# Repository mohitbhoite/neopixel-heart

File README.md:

# neopixel-heart
A simple heart shaped PCB with neopixels powered by Particle Photon or Spark Core

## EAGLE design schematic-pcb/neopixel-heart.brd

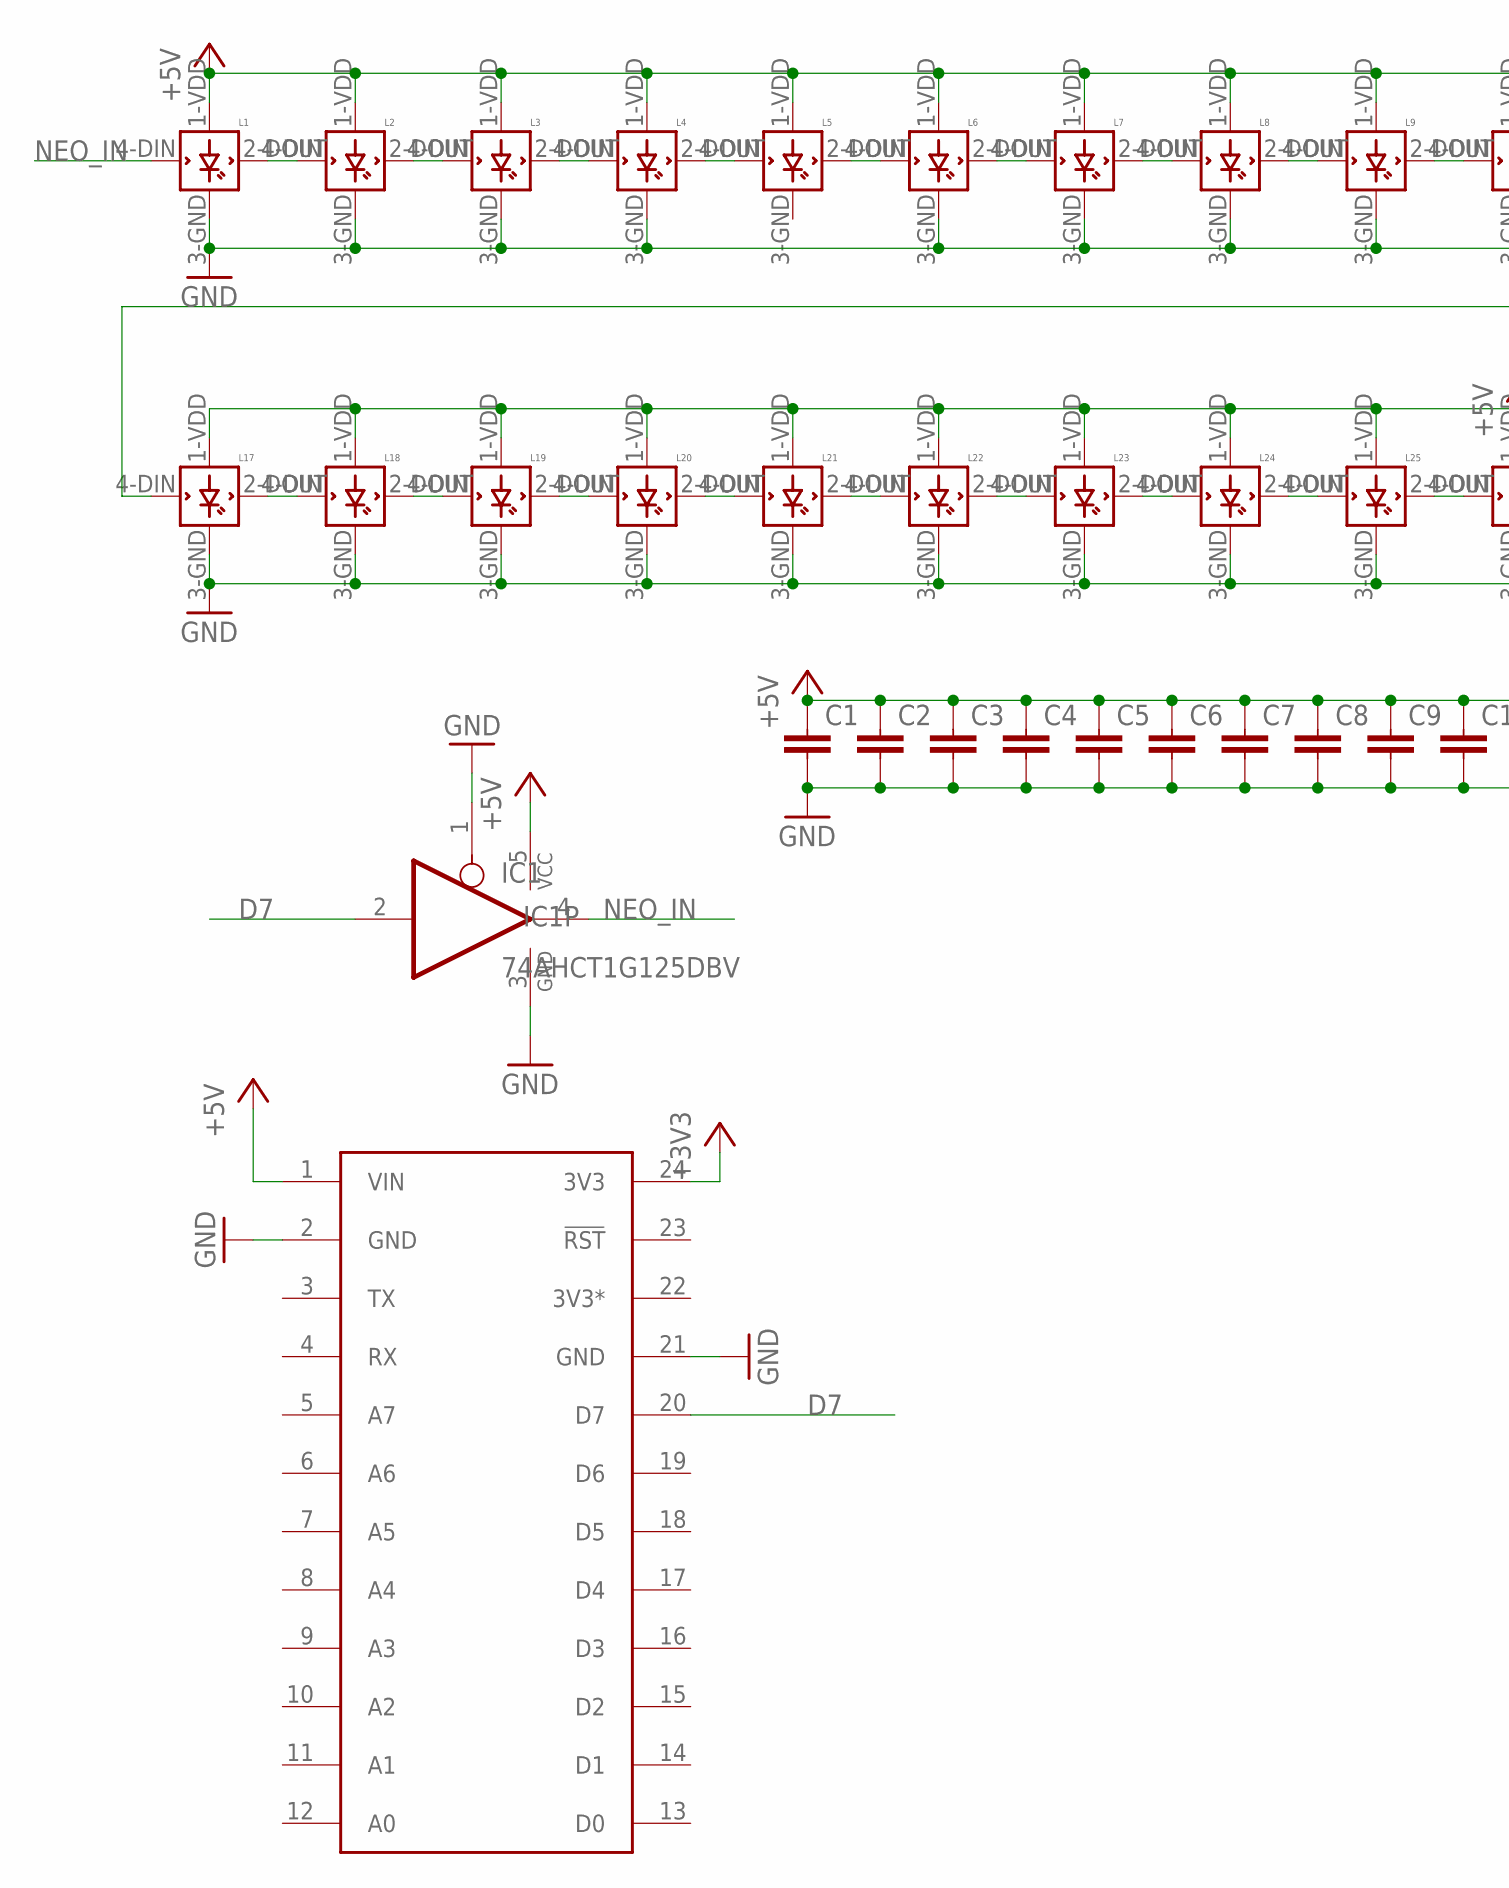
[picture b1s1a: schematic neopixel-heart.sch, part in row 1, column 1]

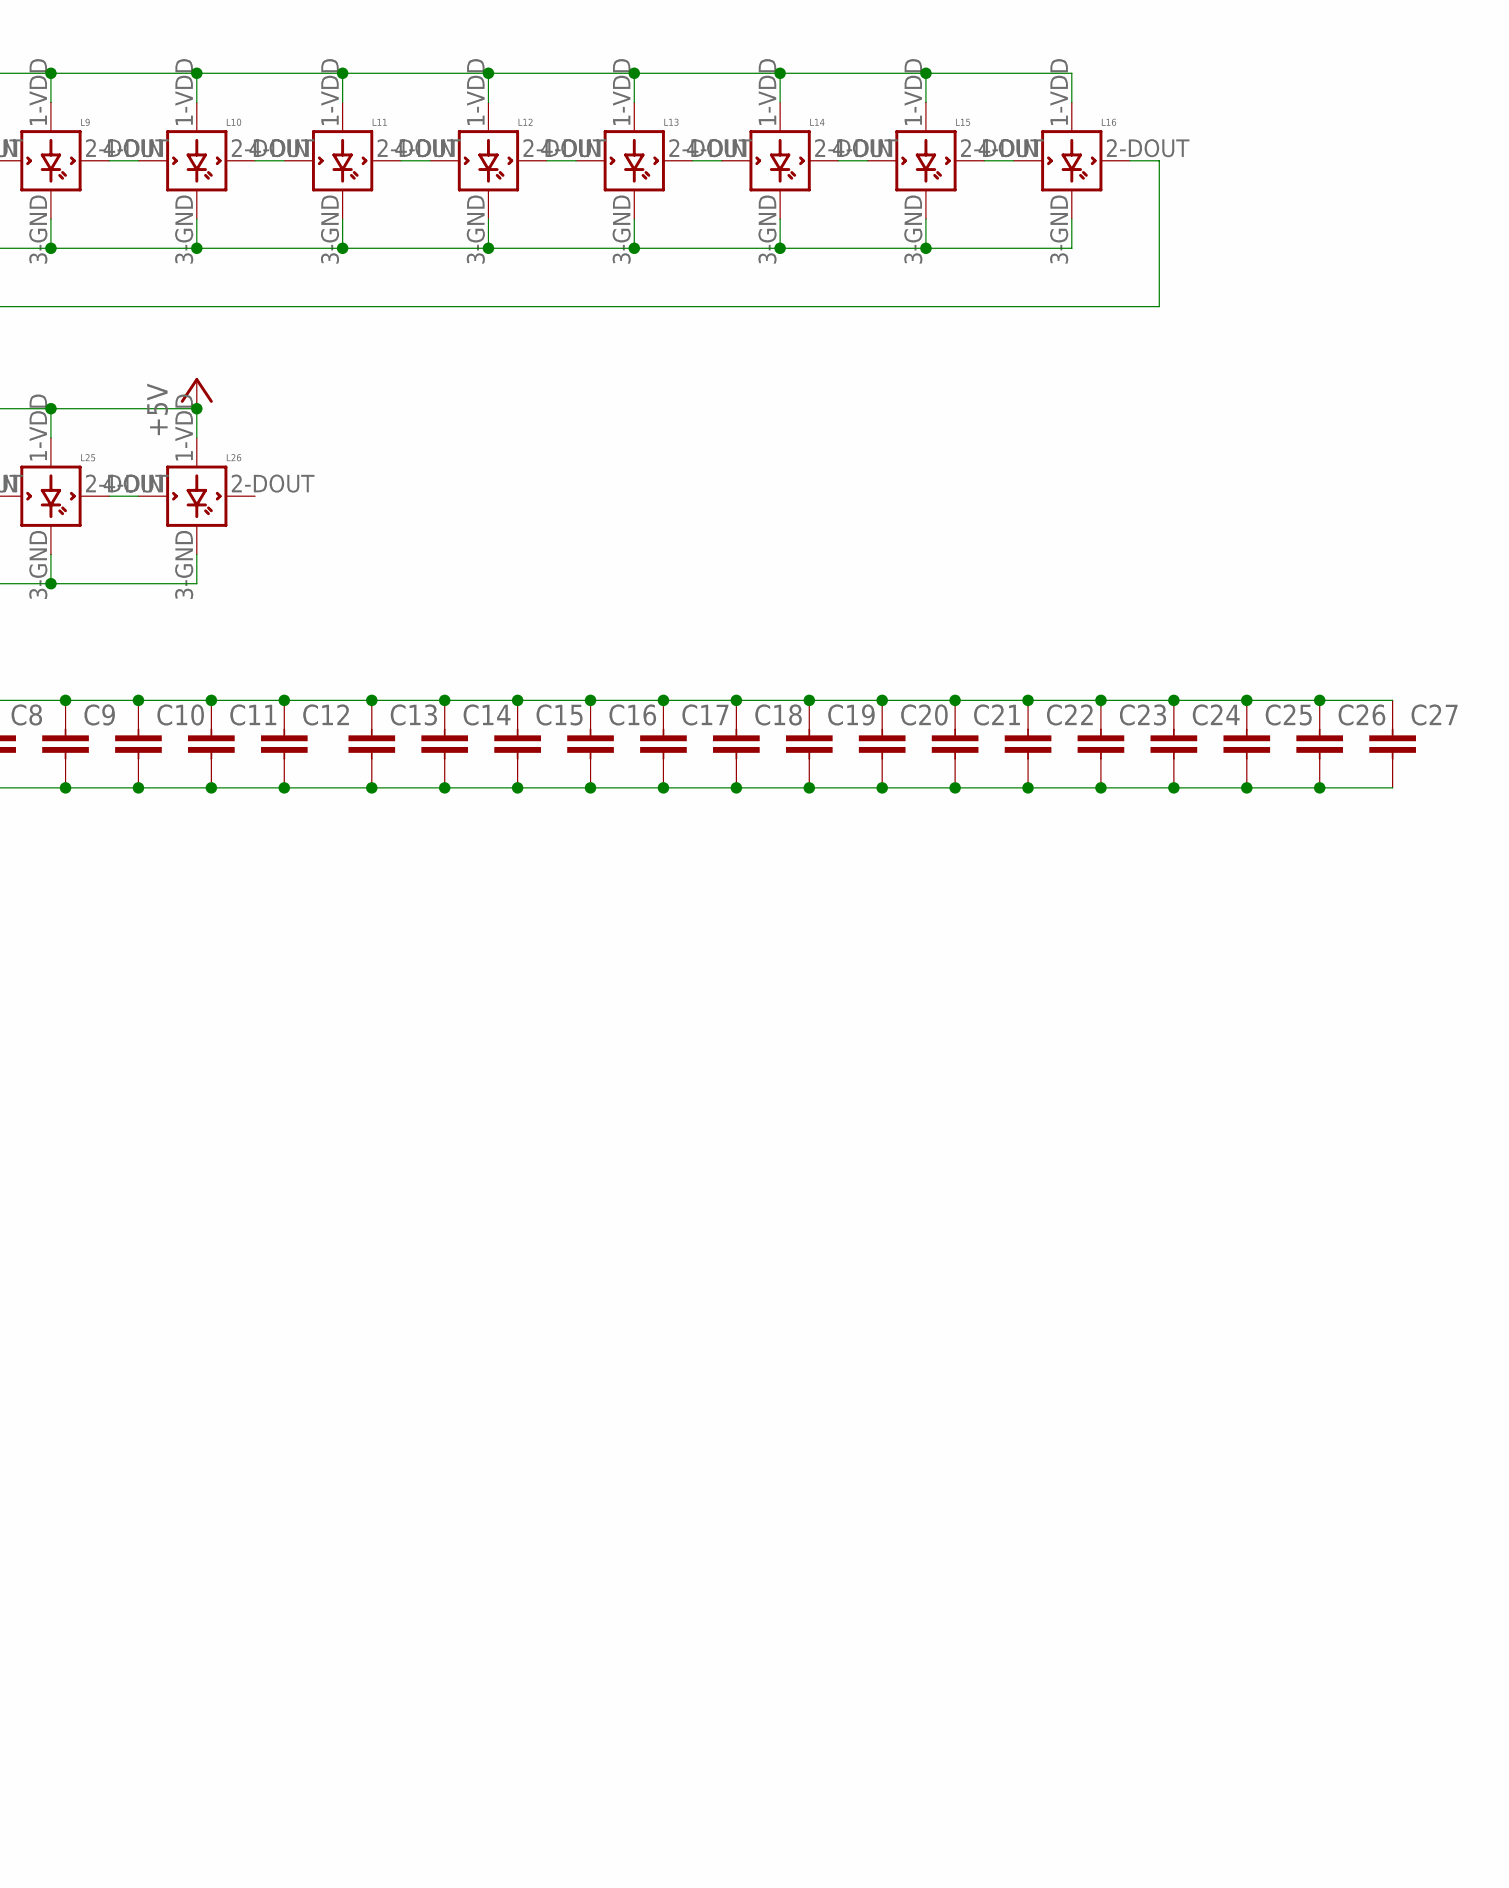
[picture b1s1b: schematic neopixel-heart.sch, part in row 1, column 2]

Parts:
C1, C2, C3, C4, C5, C6, C7, C8, C9, C10, C11, C12, C13, C14, C15, C16, C17, C18, C19, C20, C21, C22, C23, C24, C25, C26, C27: CAP0603-CAP; 0603-CAP
IC1: 74AHCT1G125DBV; SOT23-5
L1, L2, L3, L4, L5, L6, L7, L8, L9, L10, L11, L12, L13, L14, L15, L16, L17, L18, L19, L20, L21, L22, L23, L24, L25, L26: WS2812B
U$1: SPARK_CORECORE; SPARK_CORE

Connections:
3V3*: U$1.22 (3V3*)
+3V3: U$1.24 (3V3)
+5V: C1.1, C2.1, C3.1, C4.1, C5.1, C6.1, C7.1, C8.1, C9.1, C10.1, C11.1, C12.1, C13.1, C14.1, C15.1, C16.1, C17.1, C18.1, C19.1, C20.1, C21.1, C22.1, C23.1, C24.1, C25.1, C26.1, C27.1, IC1.5 (VCC), L1.1-VDD (VDD), L2.1-VDD (VDD), L3.1-VDD (VDD), L4.1-VDD (VDD), L5.1-VDD (VDD), L6.1-VDD (VDD), L7.1-VDD (VDD), L8.1-VDD (VDD), L9.1-VDD (VDD), L10.1-VDD (VDD), L11.1-VDD (VDD), L12.1-VDD (VDD), L13.1-VDD (VDD), L14.1-VDD (VDD), L15.1-VDD (VDD), L16.1-VDD (VDD), L17.1-VDD (VDD), L18.1-VDD (VDD), L19.1-VDD (VDD), L20.1-VDD (VDD), L21.1-VDD (VDD), L22.1-VDD (VDD), L23.1-VDD (VDD), L24.1-VDD (VDD), L25.1-VDD (VDD), L26.1-VDD (VDD), U$1.1 (VIN)
D7: IC1.2 (I), U$1.20 (D7)
GND: C1.2, C2.2, C3.2, C4.2, C5.2, C6.2, C7.2, C8.2, C9.2, C10.2, C11.2, C12.2, C13.2, C14.2, C15.2, C16.2, C17.2, C18.2, C19.2, C20.2, C21.2, C22.2, C23.2, C24.2, C25.2, C26.2, C27.2, IC1.1 (OE), IC1.3 (GND), L1.3-GND (GND), L2.3-GND (GND), L3.3-GND (GND), L4.3-GND (GND), L6.3-GND (GND), L7.3-GND (GND), L8.3-GND (GND), L9.3-GND (GND), L10.3-GND (GND), L11.3-GND (GND), L12.3-GND (GND), L13.3-GND (GND), L14.3-GND (GND), L15.3-GND (GND), L16.3-GND (GND), L17.3-GND (GND), L18.3-GND (GND), L19.3-GND (GND), L20.3-GND (GND), L21.3-GND (GND), L22.3-GND (GND), L23.3-GND (GND), L24.3-GND (GND), L25.3-GND (GND), U$1.2 (GND), U$1.21 (GND)
unnamed: L1.2-DOUT (DOUT), L2.4-DIN (DIN)
unnamed: L2.2-DOUT (DOUT), L3.4-DIN (DIN)
unnamed: L3.2-DOUT (DOUT), L4.4-DIN (DIN)
unnamed: L4.2-DOUT (DOUT), L5.4-DIN (DIN)
unnamed: L5.2-DOUT (DOUT), L6.4-DIN (DIN)
unnamed: L6.2-DOUT (DOUT), L7.4-DIN (DIN)
unnamed: L7.2-DOUT (DOUT), L8.4-DIN (DIN)
unnamed: L8.2-DOUT (DOUT), L9.4-DIN (DIN)
unnamed: L9.2-DOUT (DOUT), L10.4-DIN (DIN)
unnamed: L10.2-DOUT (DOUT), L11.4-DIN (DIN)
unnamed: L11.2-DOUT (DOUT), L12.4-DIN (DIN)
unnamed: L12.2-DOUT (DOUT), L13.4-DIN (DIN)
unnamed: L13.2-DOUT (DOUT), L14.4-DIN (DIN)
unnamed: L14.2-DOUT (DOUT), L15.4-DIN (DIN)
unnamed: L15.2-DOUT (DOUT), L16.4-DIN (DIN)
unnamed: L17.2-DOUT (DOUT), L18.4-DIN (DIN)
unnamed: L18.2-DOUT (DOUT), L19.4-DIN (DIN)
unnamed: L19.2-DOUT (DOUT), L20.4-DIN (DIN)
unnamed: L20.2-DOUT (DOUT), L21.4-DIN (DIN)
unnamed: L21.2-DOUT (DOUT), L22.4-DIN (DIN)
unnamed: L22.2-DOUT (DOUT), L23.4-DIN (DIN)
unnamed: L23.2-DOUT (DOUT), L24.4-DIN (DIN)
unnamed: L24.2-DOUT (DOUT), L25.4-DIN (DIN)
unnamed: L25.2-DOUT (DOUT), L26.4-DIN (DIN)
unnamed: L16.2-DOUT (DOUT), L17.4-DIN (DIN)
NEO_IN: IC1.4 (O), L1.4-DIN (DIN)

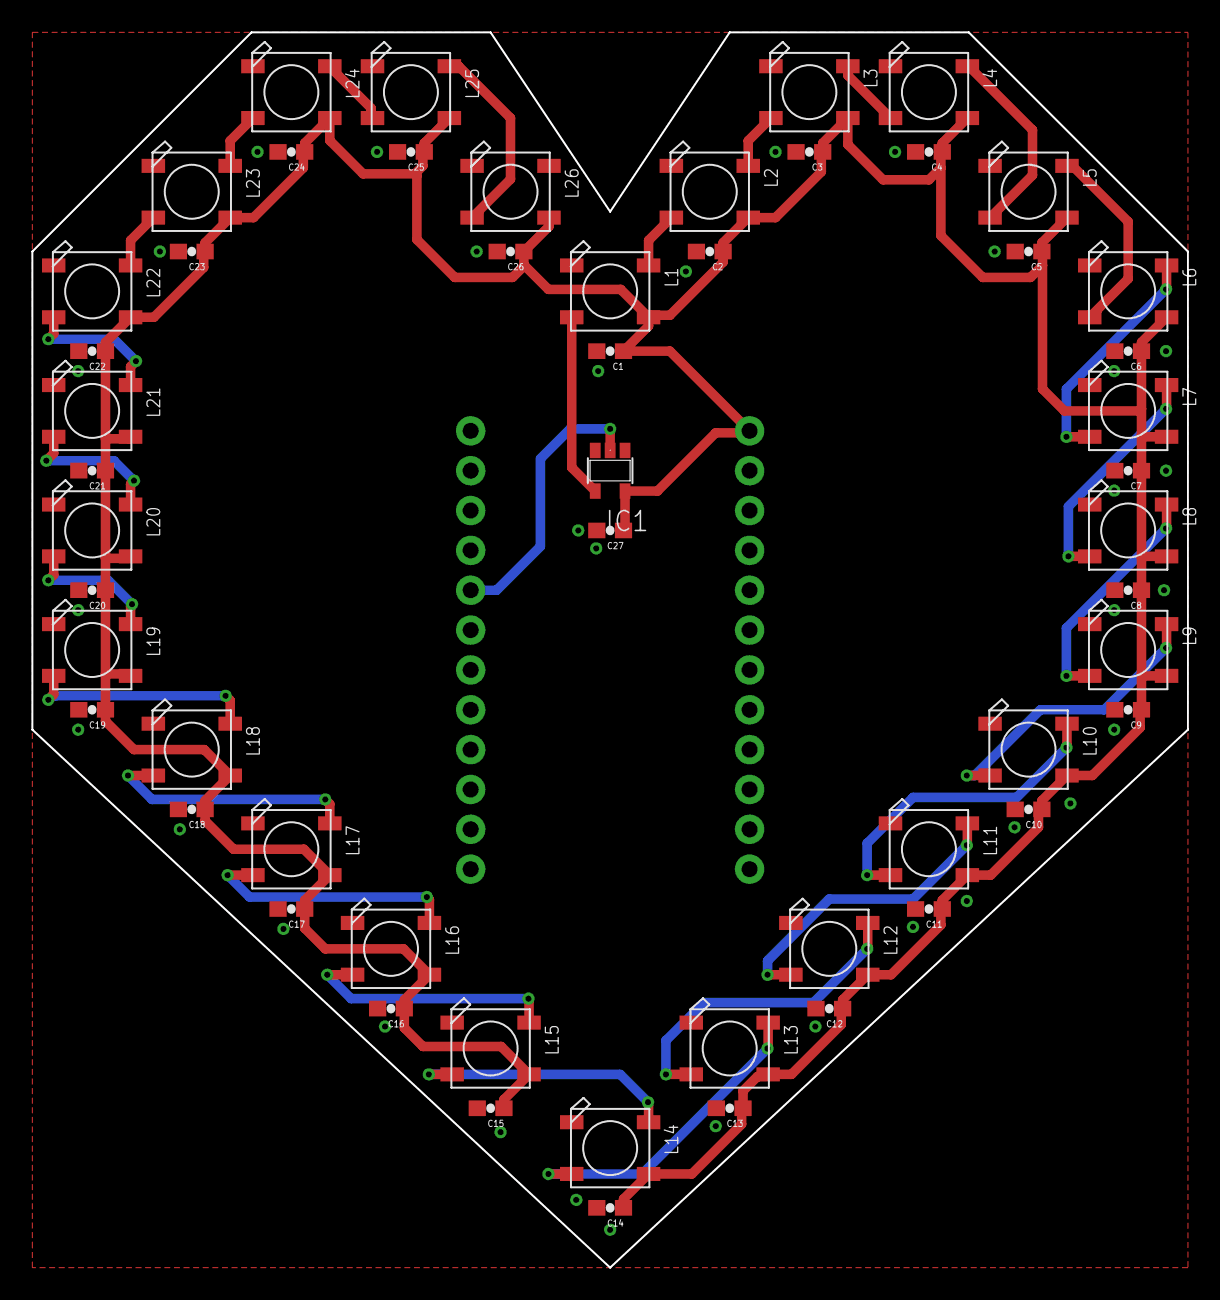
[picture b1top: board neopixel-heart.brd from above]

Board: 2 copper layers, 73.7 x 78.7 mm, 55 parts (1 on the bottom side), 29 nets.

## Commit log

2019-03-05 added design files

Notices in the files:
parts and their libraries:
SparkFun-Passives: Licensing: Creative Commons ShareAlike 4.0 International - https://creativecommons.org/licenses/by-sa/4.0
